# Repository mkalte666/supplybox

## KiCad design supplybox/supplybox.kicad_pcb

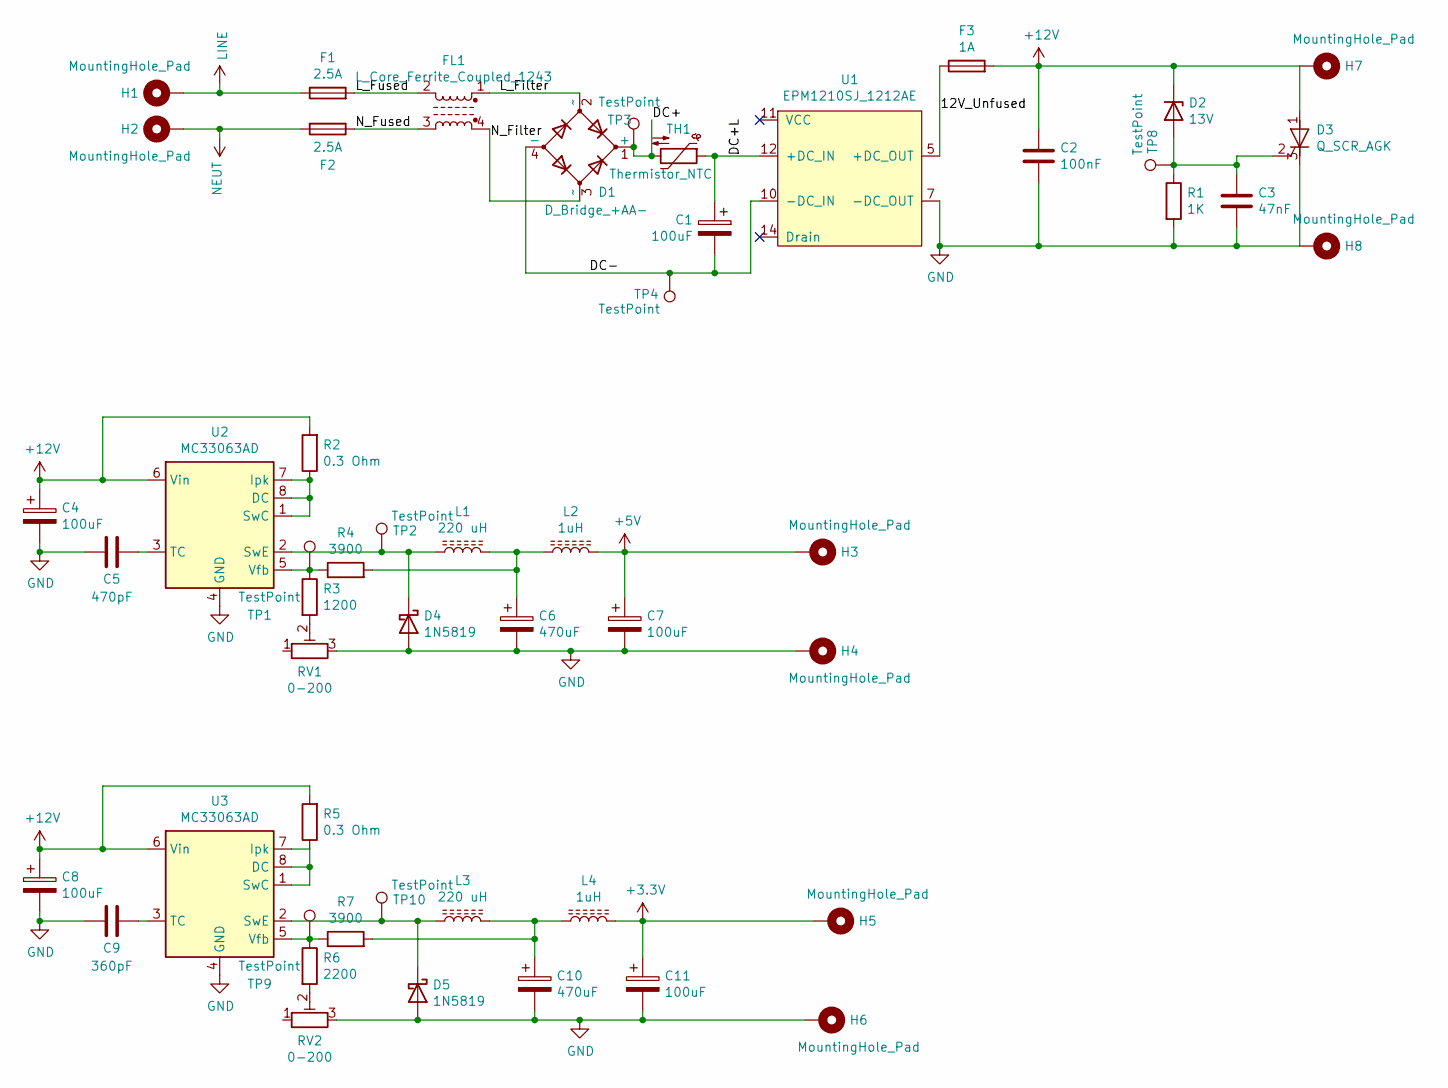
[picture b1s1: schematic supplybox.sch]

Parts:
C1: 100uF; CP_Radial_D18.0mm_P7.50mm; digikey 565-1481-ND
C2: 100nF; C_0603_1608Metric_Pad1.08x0.95mm_HandSolder; digikey 1276-1099-1-ND
C3: 47nF; C_0603_1608Metric_Pad1.08x0.95mm_HandSolder; digikey 1292-1446-1-ND
C4, C7, C8, C11: 100uF; C_Elec_6.3x7.7; digikey PCE3797CT-ND
C5: 470pF; C_0603_1608Metric_Pad1.08x0.95mm_HandSolder; digikey 1292-1530-1-ND
C6, C10: 470uF; CP_Elec_10x10.5; digikey PCE3805CT-ND
C9: 360pF; C_0603_1608Metric_Pad1.08x0.95mm_HandSolder; digikey 478-10353-1-ND
D1: D_Bridge_+AA-; KBP20XXG; digikey KBP206GDI-ND
D2: 13V; D_SOT-23_ANK; digikey BZX84C13LT1GOSCT-ND
D3: Q_SCR_AGK; TO-92_Inline_Wide; digikey 1740-1089-1-ND
D4, D5: 1N5819; D_SOD-123F; digikey NTS245SFT1GOSCT-ND
F1, F2: 2.5A; RST_XXX; digikey 507-2365-1-ND
F3: 1A; Fuse_0805_2012Metric_Pad1.15x1.40mm_HandSolder; digikey MFU08051.00CT-ND
FL1: L_Core_Ferrite_Coupled_1243; L_CommonMode_Wuerth_WE-CMB-XS; digikey 732-14016-ND
H1, H2, H3, H4, H5, H6, H7, H8: MountingHole_Pad; MountingHole_3.2mm_M3_DIN965_Pad
L1, L3: 220 uH; L_Radial_D9.5mm_P5.00mm_Fastron_07HVP; digikey RLB9012-221KL-ND
L2, L4: 1uH; L_0805_2012Metric_Pad1.15x1.40mm_HandSolder; digikey 445-6756-1-ND
R1: 1K; R_0603_1608Metric_Pad0.98x0.95mm_HandSolder; digikey RHM1.0KDCT-ND
R2, R5: 0.3 Ohm; R_0805_2012Metric_Pad1.20x1.40mm_HandSolder; digikey RL12S.30FDKR-ND‎
R3: 1200; R_0603_1608Metric_Pad0.98x0.95mm_HandSolder; digikey RR08P1.2KDCT-ND
R4: 3900; R_0603_1608Metric_Pad0.98x0.95mm_HandSolder; digikey RR08P3.9KDCT-ND
R6: 2200; R_0603_1608Metric_Pad0.98x0.95mm_HandSolder; digikey RR0816P-222-D
R7: 3900; R_0603_1608Metric_Pad0.98x0.95mm_HandSolder; digikey RR08P1.2KDCT-ND
RV1, RV2: 0-200; Potentiometer_Bourns_TC33X_Vertical; digikey TC33X-2-201ECT-ND
TH1: Thermistor_NTC; R_Axial_DIN0204_L3.6mm_D1.6mm_P5.08mm_Horizontal; digikey 495-76103-1-ND
TP1, TP2, TP3, TP4, TP8, TP9, TP10: TestPoint; TestPoint_Pad_D1.0mm
U1: EPM1210SJ_1212AE; EPMXX10SJ_XXXXAE; digikey MT7382-ND
U2, U3: MC33063AD; SOIC-8_3.9x4.9mm_P1.27mm; digikey 296-17763-1-ND

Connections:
+3V3: C11.1, H5.1, L4.2
+5V: C7.1, H3.1, L2.2
+12V: C2.1, C4.1, C8.1, D2.1 (K), D3.1 (A), F3.2, H7.1, R2.2, R5.2, U2.6 (Vin), U3.6 (Vin)
/12V_Unfused: F3.1, U1.5 (+DC_OUT)
/DC+: D1.1 (+), TH1.2, TP3.1
/DC+L: C1.1, TH1.1, U1.12 (+DC_IN)
/DC-: C1.2, D1.4 (-), TP4.1, U1.10 (-DC_IN)
/L_Filter: D1.2 (~~), FL1.1
/L_Fused: F1.2, FL1.2
/N_Filter: D1.3 (~~), FL1.4
/N_Fused: F2.1, FL1.3
GND: C2.2, C3.2, C4.2, C5.1, C6.2, C7.2, C8.2, C9.1, C10.2, C11.2, D3.3 (K), D4.2 (A), D5.2 (A), H4.1, H6.1, H8.1, R1.2, RV1.3, RV2.3, U1.7 (-DC_OUT), U2.4 (GND), U3.4 (GND)
LINE: F1.1, H1.1
NEUT: F2.2, H2.1
unnamed: C3.1, D2.2 (A), D3.2 (G), R1.1, TP8.1
unnamed: C5.2, U2.3 (TC)
unnamed: C6.1, L1.2, L2.1, R4.2
unnamed: C9.2, U3.3 (TC)
unnamed: C10.1, L3.2, L4.1, R7.2
unnamed: D4.1 (K), L1.1, TP2.1, U2.2 (SwE)
unnamed: D5.1 (K), L3.1, TP10.1, U3.2 (SwE)
unnamed: R2.1, U2.1 (SwC), U2.7 (Ipk), U2.8 (DC)
unnamed: R3.1, R4.1, TP1.1, U2.5 (Vfb)
unnamed: R3.2, RV1.2
unnamed: R5.1, U3.1 (SwC), U3.7 (Ipk), U3.8 (DC)
unnamed: R6.1, R7.1, TP9.1, U3.5 (Vfb)
unnamed: R6.2, RV2.2

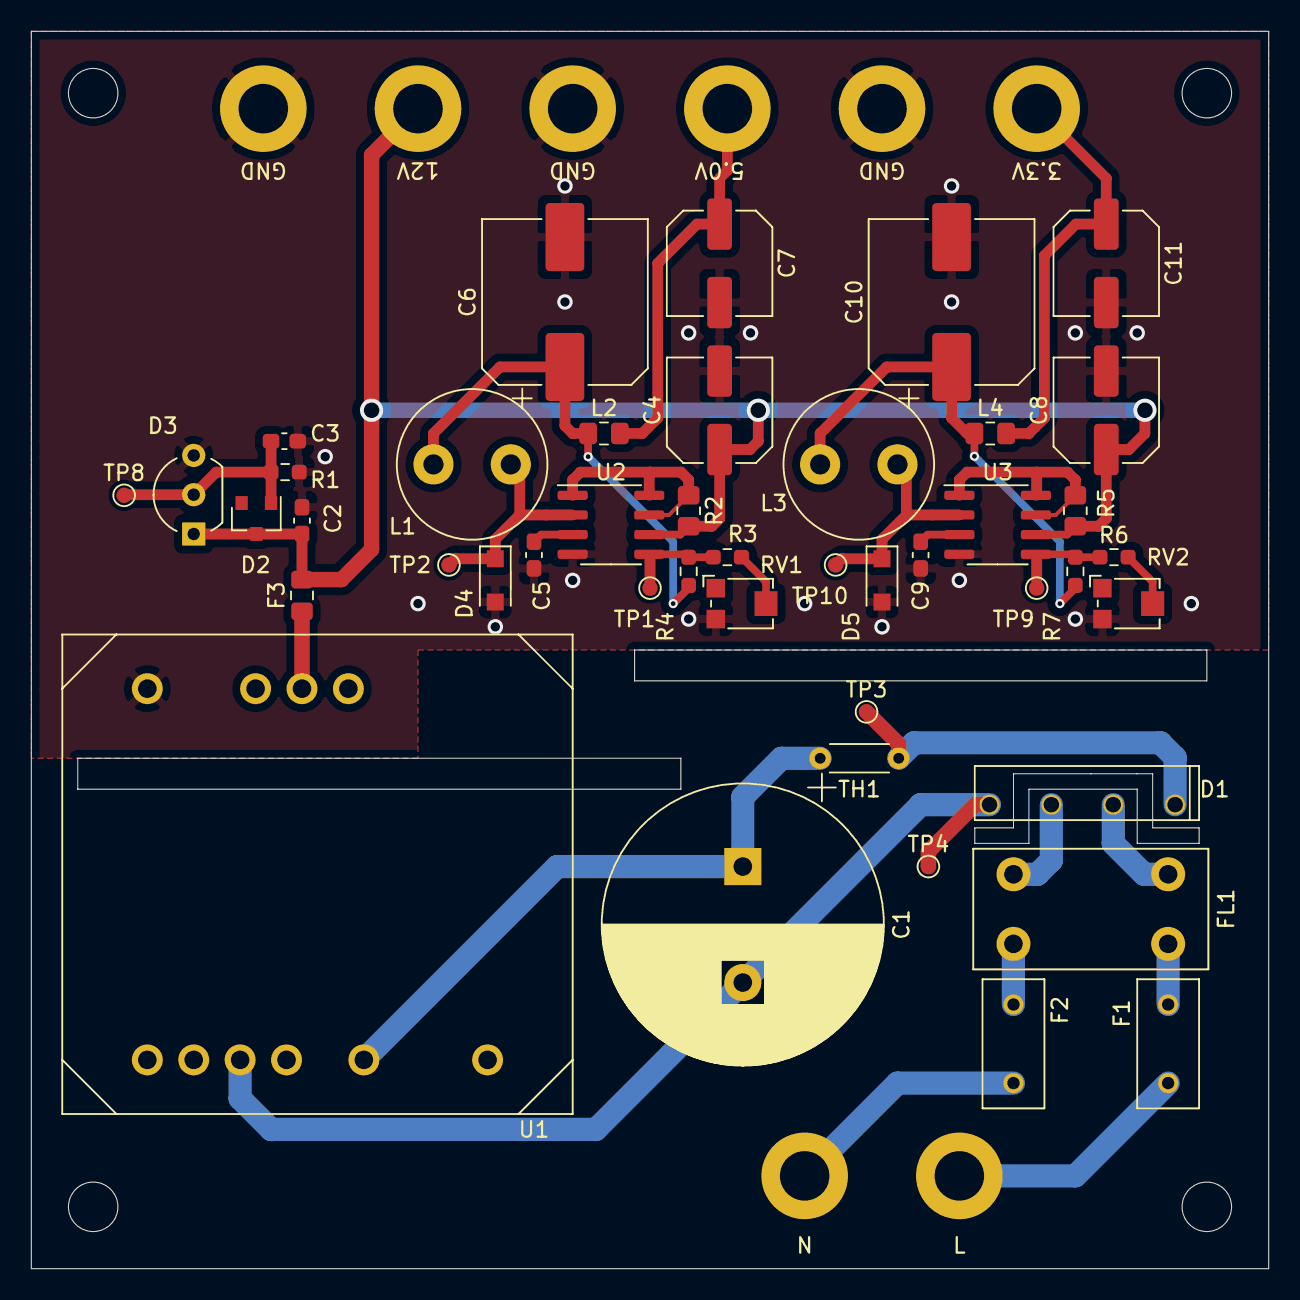
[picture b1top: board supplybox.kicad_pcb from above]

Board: 2 copper layers, 80.0 x 80.0 mm, 52 parts (0 on the bottom side), 27 nets.

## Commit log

2020-11-02 erig kicad libs
2020-11-02 update lib
2020-11-13 v1.0
2020-11-17 box ideas
2020-11-18 redo pcb and fix issues with schematic
2020-11-19 fix submodule origin
2020-11-19 Create LICENSE
